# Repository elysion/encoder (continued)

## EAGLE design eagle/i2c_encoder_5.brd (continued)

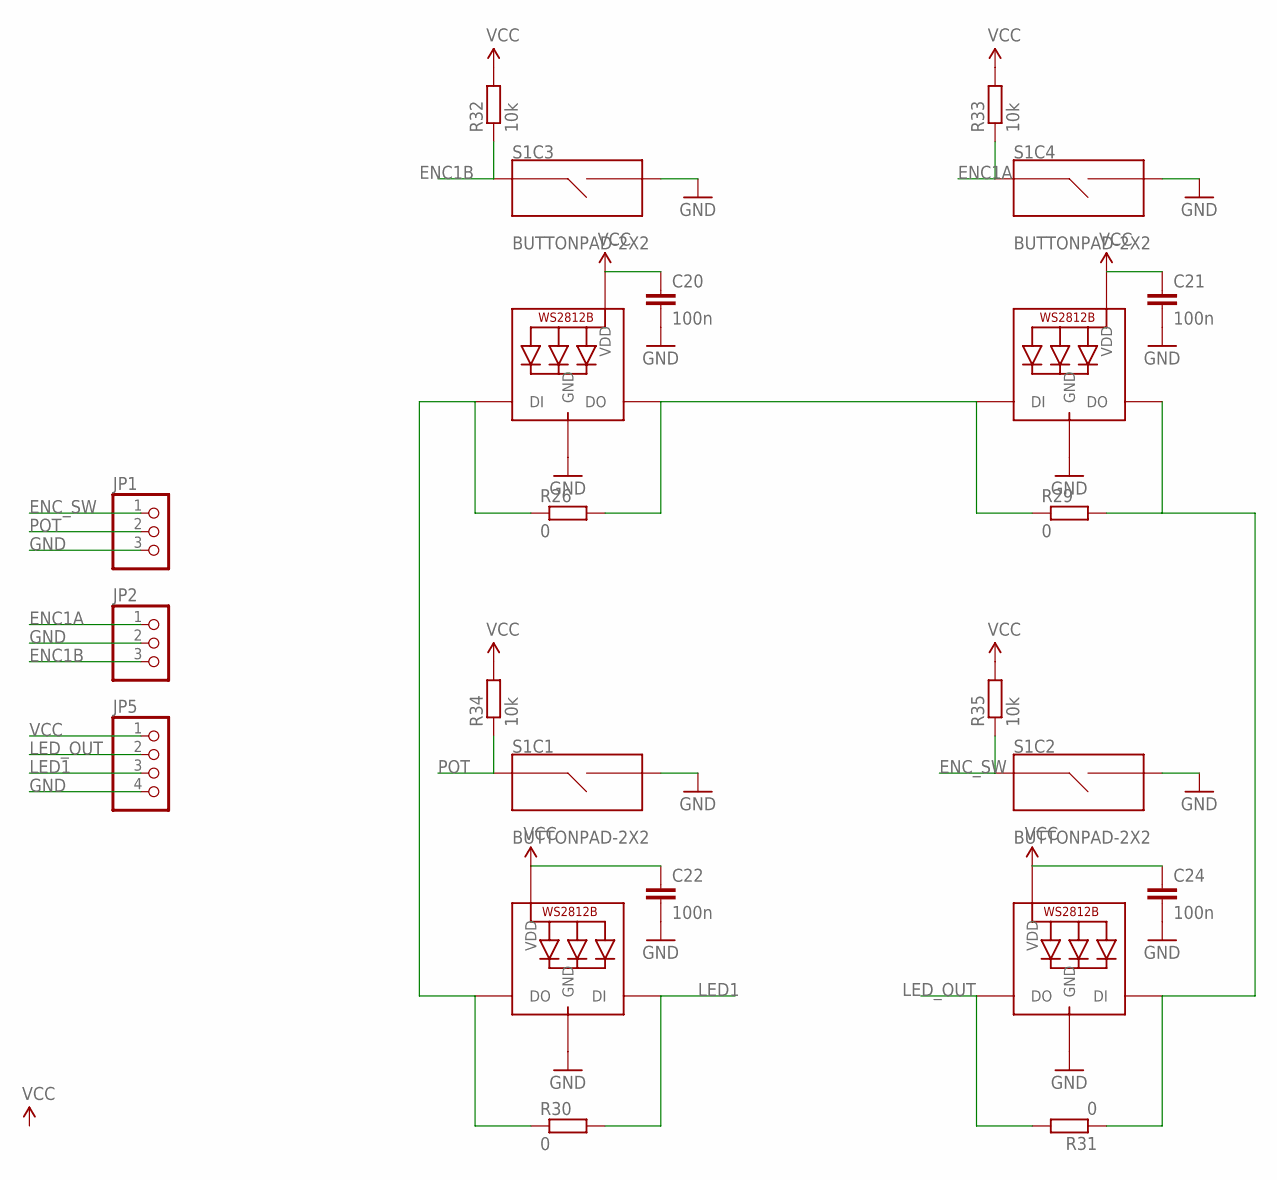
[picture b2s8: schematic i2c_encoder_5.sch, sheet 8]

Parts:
C20, C21, C22, C24: 100n; 0603-CAP
JP1, JP2: PINHD-1X31X03_SMT; 1X03_SMT
JP5: PINHD-1X41X04_SMT; 1X04_SMT
LED16, LED17, LED18, LED19: WS2812B3535; LED3535
R26, R29, R30, R31: 0; R0603
R32, R33, R34, R35: 10k; R0603
S1: BUTTONPAD-2X2; BUTTONPAD-2X2-SINGLE

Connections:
ENC1A: JP2.1, R33.1, S1.SIG7 (SIG1); also elsewhere on the board
ENC1B: JP2.3, R32.1, S1.SIG5 (SIG1); also elsewhere on the board
ENC_SW: JP1.1, R35.1, S1.SIG3 (SIG1); also elsewhere on the board
GND: C20.2, C21.2, C22.2, C24.2, JP1.3, JP2.2, JP5.4, LED16.4 (GND), LED17.4 (GND), LED18.4 (GND), LED19.4 (GND), S1.SIG2, S1.SIG4 (SIG2), S1.SIG6 (SIG2), S1.SIG8 (SIG2); also elsewhere on the board
LED1: JP5.3, LED16.1 (DI), R30.2; also elsewhere on the board
LED_OUT: JP5.2, LED17.3 (DO), R31.2; also elsewhere on the board
unnamed: LED16.3 (DO), LED18.1 (DI), R26.1, R30.1
unnamed: LED17.1 (DI), LED19.3 (DO), R29.2, R31.1
unnamed: LED18.3 (DO), LED19.1 (DI), R26.2, R29.1
POT: JP1.2, R34.1, S1.SIG1; also elsewhere on the board
VCC: C20.1, C21.1, C22.1, C24.1, JP5.1, LED16.2 (VDD), LED17.2 (VDD), LED18.2 (VDD), LED19.2 (VDD), R32.2, R33.2, R34.2, R35.2; also elsewhere on the board

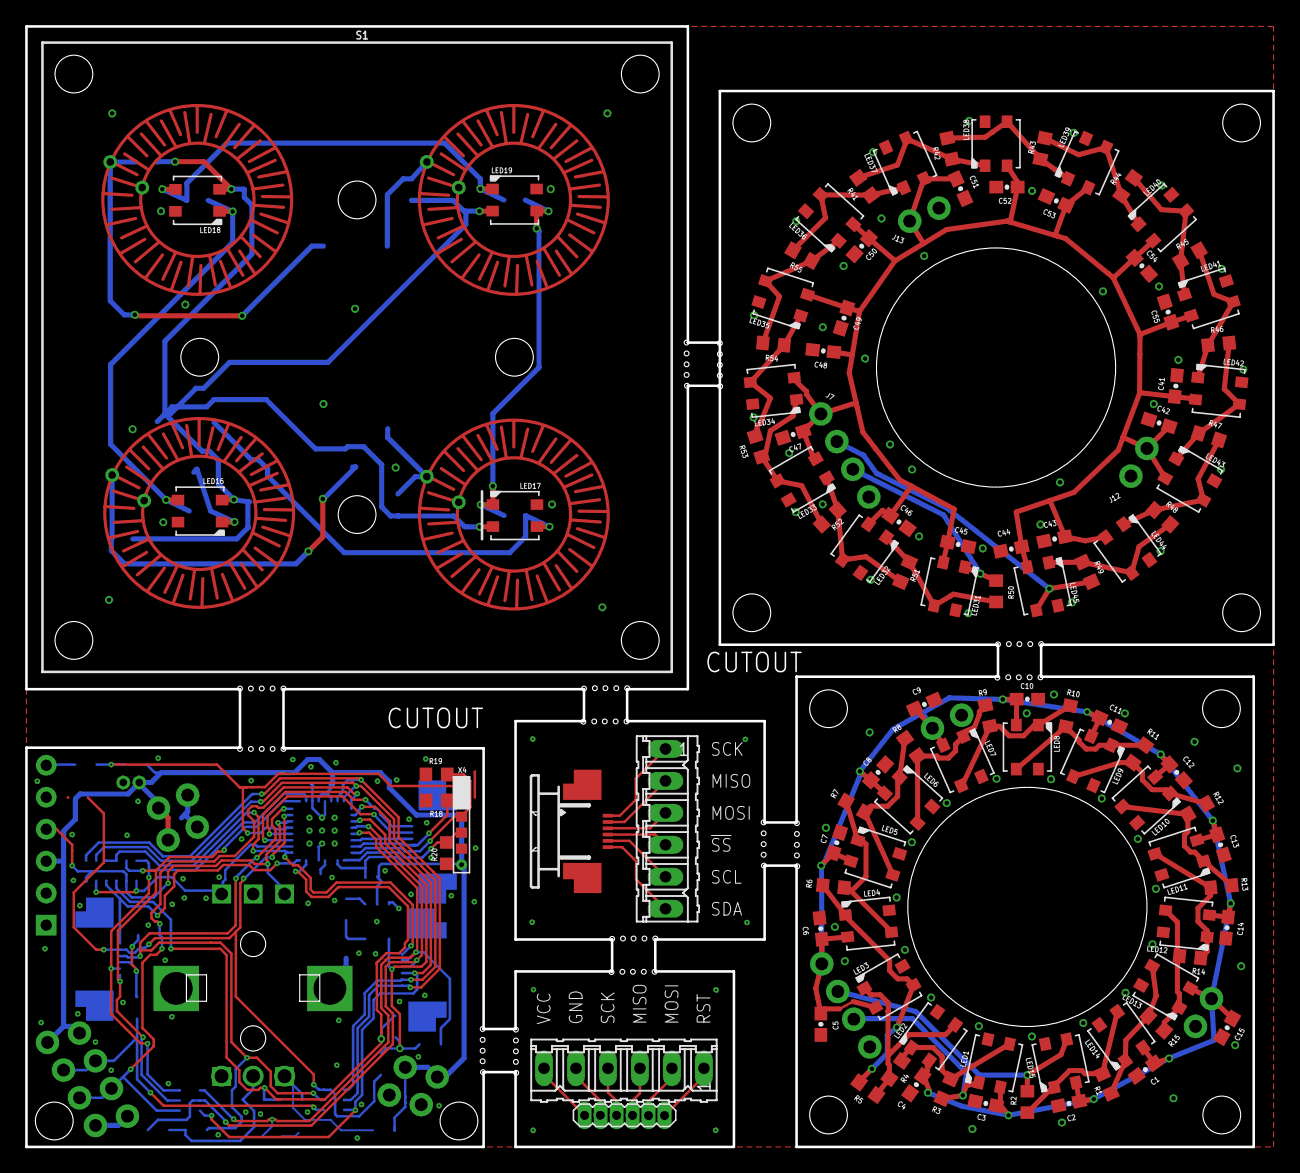
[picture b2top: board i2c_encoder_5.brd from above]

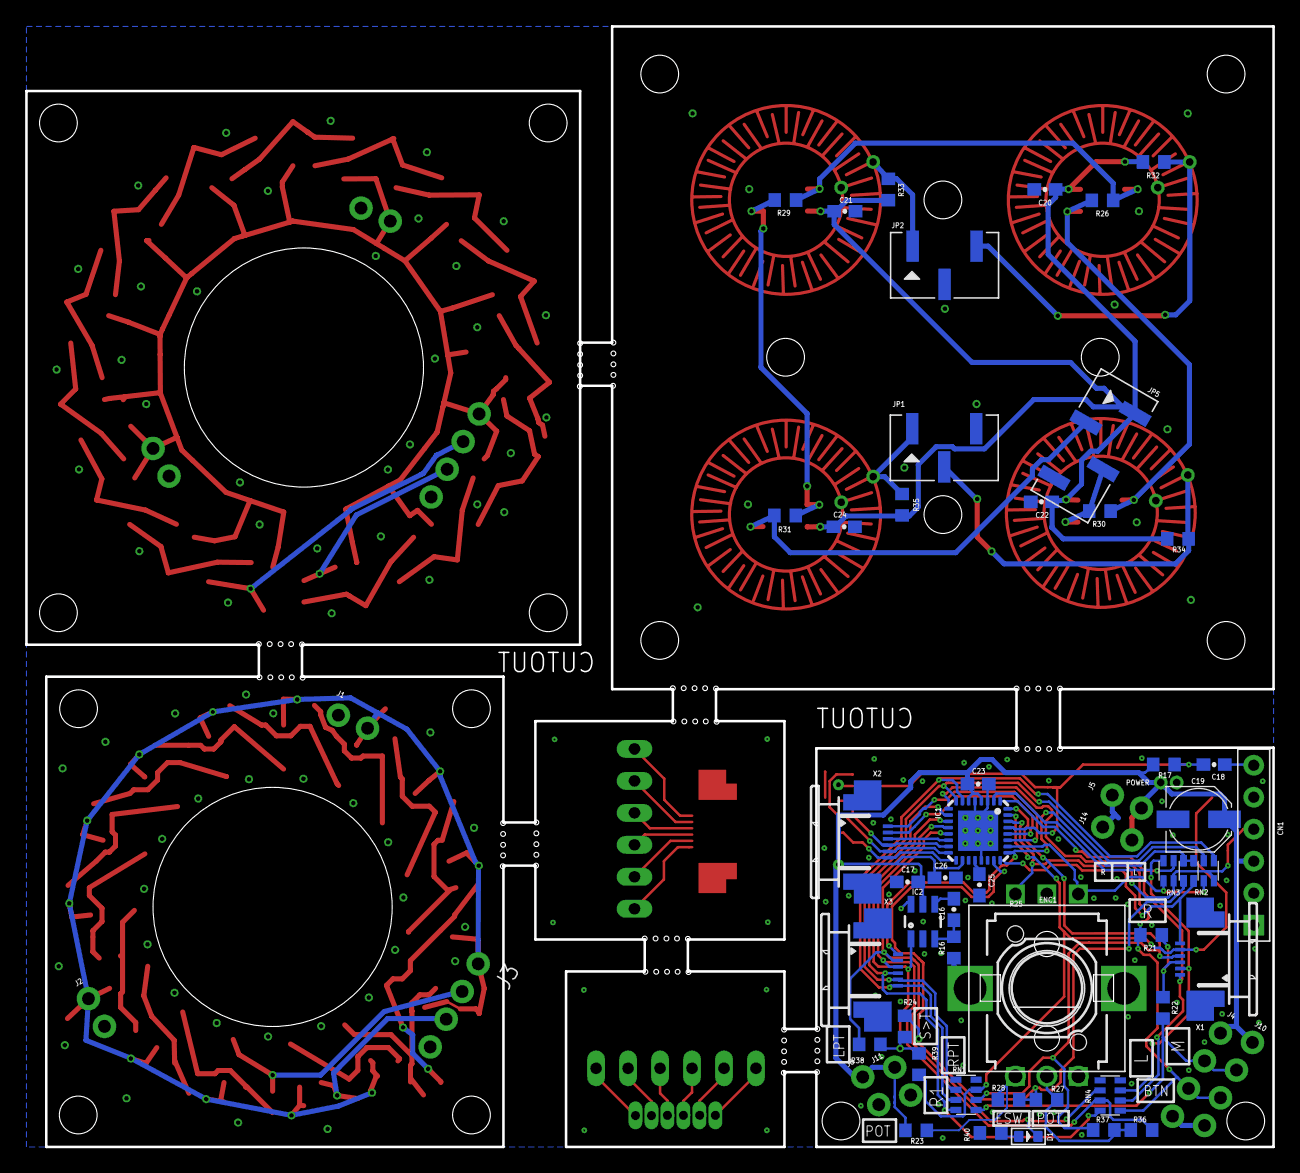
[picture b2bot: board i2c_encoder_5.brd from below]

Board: 2 copper layers, 99.1 x 89.0 mm, 166 parts (61 on the bottom side), 69 nets.
